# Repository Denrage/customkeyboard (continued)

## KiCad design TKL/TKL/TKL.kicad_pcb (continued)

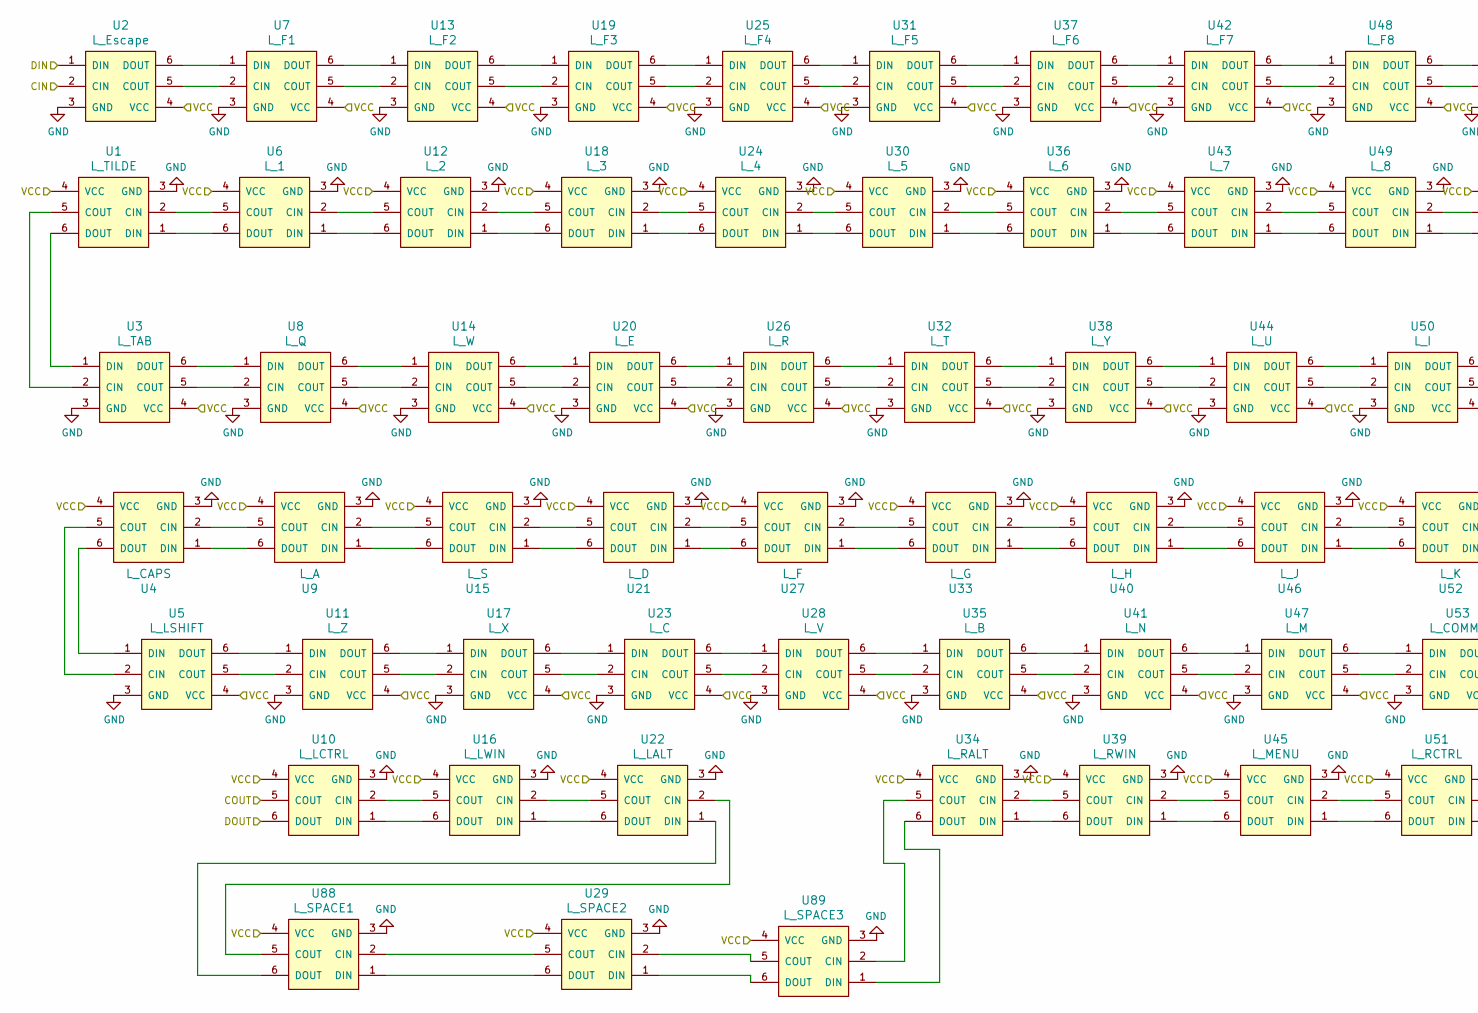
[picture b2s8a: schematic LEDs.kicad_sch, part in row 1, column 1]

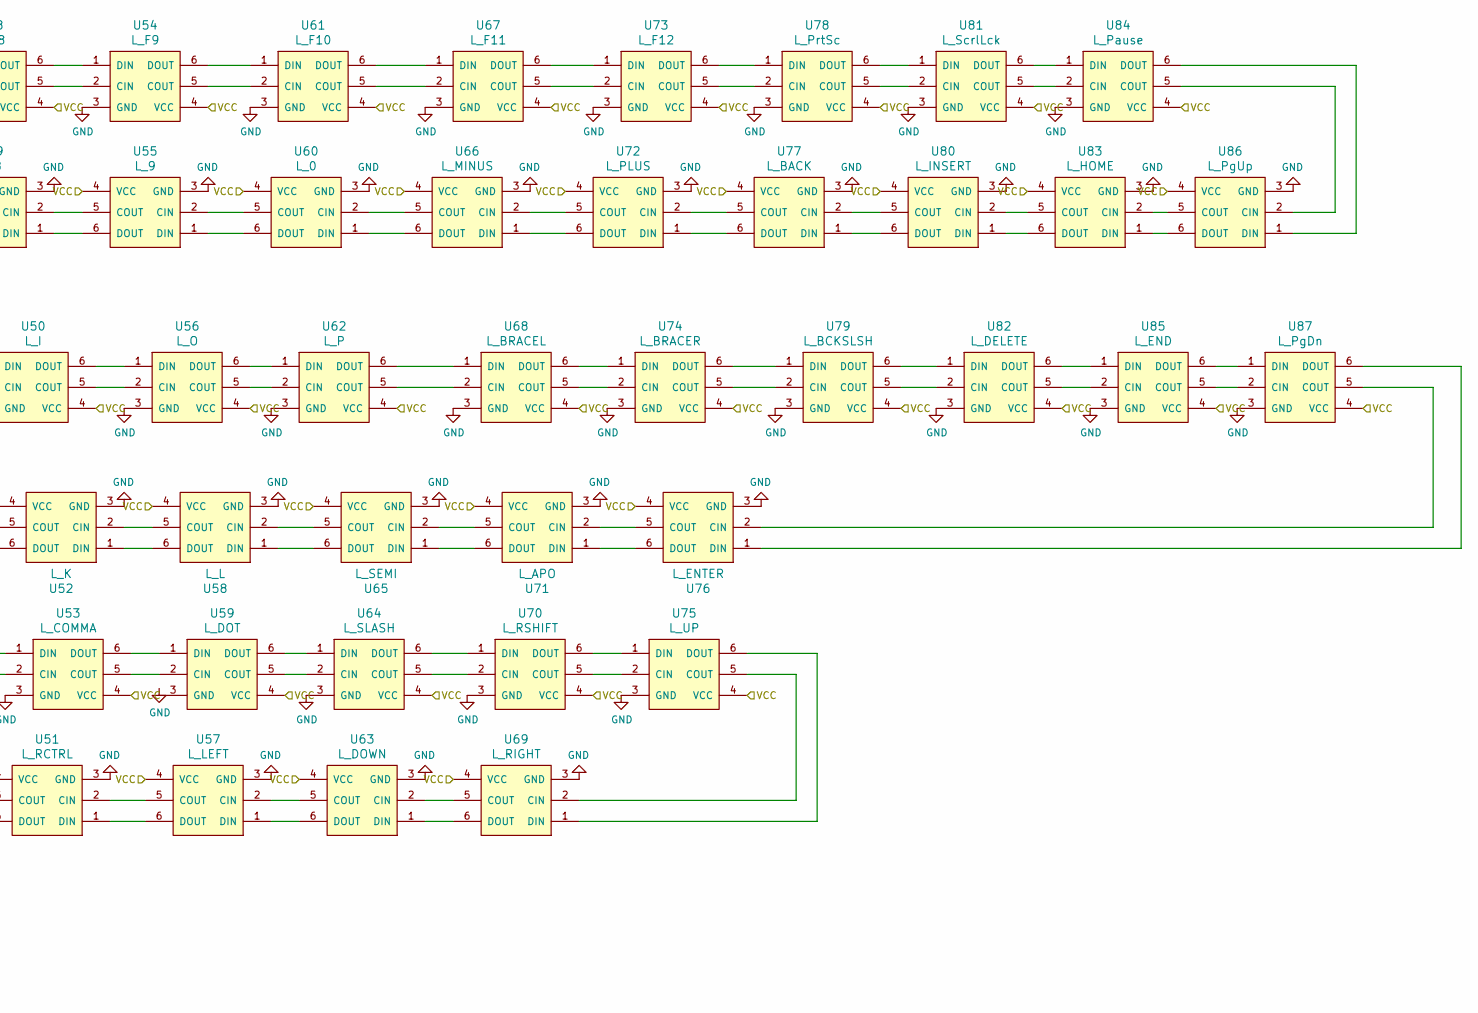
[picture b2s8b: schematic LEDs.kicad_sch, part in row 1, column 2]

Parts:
U1: L_TILDE; APA102
U2: L_Escape; APA102
U3: L_TAB; APA102
U4: L_CAPS; APA102
U5: L_LSHIFT; APA102
U6: L_1; APA102
U7: L_F1; APA102
U8: L_Q; APA102
U9: L_A; APA102
U10: L_LCTRL; APA102
U11: L_Z; APA102
U12: L_2; APA102
U13: L_F2; APA102
U14: L_W; APA102
U15: L_S; APA102
U16: L_LWIN; APA102
U17: L_X; APA102
U18: L_3; APA102
U19: L_F3; APA102
U20: L_E; APA102
U21: L_D; APA102
U22: L_LALT; APA102
U23: L_C; APA102
U24: L_4; APA102
U25: L_F4; APA102
U26: L_R; APA102
U27: L_F; APA102
U28: L_V; APA102
U29: L_SPACE2; APA102
U30: L_5; APA102
U31: L_F5; APA102
U32: L_T; APA102
U33: L_G; APA102
U34: L_RALT; APA102
U35: L_B; APA102
U36: L_6; APA102
U37: L_F6; APA102
U38: L_Y; APA102
U39: L_RWIN; APA102
U40: L_H; APA102
U41: L_N; APA102
U42: L_F7; APA102
U43: L_7; APA102
U44: L_U; APA102
U45: L_MENU; APA102
U46: L_J; APA102
U47: L_M; APA102
U48: L_F8; APA102
U49: L_8; APA102
U50: L_I; APA102
U51: L_RCTRL; APA102
U52: L_K; APA102
U53: L_COMMA; APA102
U54: L_F9; APA102
U55: L_9; APA102
U56: L_O; APA102
U57: L_LEFT; APA102
U58: L_L; APA102
U59: L_DOT; APA102
U60: L_0; APA102
U61: L_F10; APA102
U62: L_P; APA102
U63: L_DOWN; APA102
U64: L_SLASH; APA102
U65: L_SEMI; APA102
U66: L_MINUS; APA102
U67: L_F11; APA102
U68: L_BRACEL; APA102
U69: L_RIGHT; APA102
U70: L_RSHIFT; APA102
U71: L_APO; APA102
U72: L_PLUS; APA102
U73: L_F12; APA102
U74: L_BRACER; APA102
U75: L_UP; APA102
U76: L_ENTER; APA102
U77: L_BACK; APA102
U78: L_PrtSc; APA102
U79: L_BCKSLSH; APA102
U80: L_INSERT; APA102
U81: L_ScrlLck; APA102
U82: L_DELETE; APA102
U83: L_HOME; APA102
U84: L_Pause; APA102
U85: L_END; APA102
U86: L_PgUp; APA102
U87: L_PgDn; APA102
U88: L_SPACE1; APA102
U89: L_SPACE3; APA102

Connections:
CIN: U2.2 (CIN)
DIN: U2.1 (DIN)
GND: U1.3 (GND), U2.3 (GND), U3.3 (GND), U4.3 (GND), U5.3 (GND), U6.3 (GND), U7.3 (GND), U8.3 (GND), U9.3 (GND), U10.3 (GND), U11.3 (GND), U12.3 (GND), U13.3 (GND), U14.3 (GND), U15.3 (GND), U16.3 (GND), U17.3 (GND), U18.3 (GND), U19.3 (GND), U20.3 (GND), U21.3 (GND), U22.3 (GND), U23.3 (GND), U24.3 (GND), U25.3 (GND), U26.3 (GND), U27.3 (GND), U28.3 (GND), U29.3 (GND), U30.3 (GND), U31.3 (GND), U32.3 (GND), U33.3 (GND), U34.3 (GND), U35.3 (GND), U36.3 (GND), U37.3 (GND), U38.3 (GND), U39.3 (GND), U40.3 (GND), U41.3 (GND), U42.3 (GND), U43.3 (GND), U44.3 (GND), U45.3 (GND), U46.3 (GND), U47.3 (GND), U48.3 (GND), U49.3 (GND), U50.3 (GND), U51.3 (GND), U52.3 (GND), U53.3 (GND), U54.3 (GND), U55.3 (GND), U56.3 (GND), U57.3 (GND), U58.3 (GND), U60.3 (GND), U61.3 (GND), U62.3 (GND), U63.3 (GND), U64.3 (GND), U65.3 (GND), U66.3 (GND), U67.3 (GND), U68.3 (GND), U69.3 (GND), U70.3 (GND), U71.3 (GND), U72.3 (GND), U73.3 (GND), U74.3 (GND), U75.3 (GND), U76.3 (GND), U77.3 (GND), U78.3 (GND), U79.3 (GND), U80.3 (GND), U81.3 (GND), U82.3 (GND), U83.3 (GND), U84.3 (GND), U85.3 (GND), U86.3 (GND), U87.3 (GND), U88.3 (GND), U89.3 (GND)
unnamed: U1.1 (DIN), U6.6 (DOUT)
unnamed: U1.2 (CIN), U6.5 (COUT)
unnamed: U1.5 (COUT), U3.2 (CIN)
unnamed: U1.6 (DOUT), U3.1 (DIN)
unnamed: U2.5 (COUT), U7.2 (CIN)
unnamed: U2.6 (DOUT), U7.1 (DIN)
unnamed: U3.5 (COUT), U8.2 (CIN)
unnamed: U3.6 (DOUT), U8.1 (DIN)
unnamed: U4.1 (DIN), U9.6 (DOUT)
unnamed: U4.2 (CIN), U9.5 (COUT)
unnamed: U4.5 (COUT), U5.2 (CIN)
unnamed: U4.6 (DOUT), U5.1 (DIN)
unnamed: U10.1 (DIN), U16.6 (DOUT)
unnamed: U10.2 (CIN), U16.5 (COUT)
unnamed: U5.6 (DOUT), U11.1 (DIN)
unnamed: U5.5 (COUT), U11.2 (CIN)
unnamed: U11.5 (COUT), U17.2 (CIN)
unnamed: U11.6 (DOUT), U17.1 (DIN)
unnamed: U12.1 (DIN), U18.6 (DOUT)
unnamed: U12.2 (CIN), U18.5 (COUT)
unnamed: U6.2 (CIN), U12.5 (COUT)
unnamed: U6.1 (DIN), U12.6 (DOUT)
unnamed: U7.6 (DOUT), U13.1 (DIN)
unnamed: U7.5 (COUT), U13.2 (CIN)
unnamed: U13.5 (COUT), U19.2 (CIN)
unnamed: U13.6 (DOUT), U19.1 (DIN)
unnamed: U8.6 (DOUT), U14.1 (DIN)
unnamed: U8.5 (COUT), U14.2 (CIN)
unnamed: U14.5 (COUT), U20.2 (CIN)
unnamed: U14.6 (DOUT), U20.1 (DIN)
unnamed: U15.1 (DIN), U21.6 (DOUT)
unnamed: U15.2 (CIN), U21.5 (COUT)
unnamed: U9.2 (CIN), U15.5 (COUT)
unnamed: U9.1 (DIN), U15.6 (DOUT)
unnamed: U16.1 (DIN), U22.6 (DOUT)
unnamed: U16.2 (CIN), U22.5 (COUT)
unnamed: U17.5 (COUT), U23.2 (CIN)
unnamed: U17.6 (DOUT), U23.1 (DIN)
unnamed: U18.1 (DIN), U24.6 (DOUT)
unnamed: U18.2 (CIN), U24.5 (COUT)
unnamed: U19.5 (COUT), U25.2 (CIN)
unnamed: U19.6 (DOUT), U25.1 (DIN)
unnamed: U20.5 (COUT), U26.2 (CIN)
unnamed: U20.6 (DOUT), U26.1 (DIN)
unnamed: U21.1 (DIN), U27.6 (DOUT)
unnamed: U21.2 (CIN), U27.5 (COUT)
unnamed: U22.1 (DIN), U88.6 (DOUT)
unnamed: U22.2 (CIN), U88.5 (COUT)
unnamed: U23.5 (COUT), U28.2 (CIN)
unnamed: U23.6 (DOUT), U28.1 (DIN)
unnamed: U24.1 (DIN), U30.6 (DOUT)
unnamed: U24.2 (CIN), U30.5 (COUT)
unnamed: U25.5 (COUT), U31.2 (CIN)
unnamed: U25.6 (DOUT), U31.1 (DIN)
unnamed: U26.5 (COUT), U32.2 (CIN)
unnamed: U26.6 (DOUT), U32.1 (DIN)
unnamed: U27.1 (DIN), U33.6 (DOUT)
unnamed: U27.2 (CIN), U33.5 (COUT)
unnamed: U28.5 (COUT), U35.2 (CIN)
unnamed: U28.6 (DOUT), U35.1 (DIN)
unnamed: U29.1 (DIN), U89.6 (DOUT)
unnamed: U29.2 (CIN), U89.5 (COUT)
unnamed: U29.5 (COUT), U88.2 (CIN)
unnamed: U29.6 (DOUT), U88.1 (DIN)
unnamed: U30.1 (DIN), U36.6 (DOUT)
unnamed: U30.2 (CIN), U36.5 (COUT)
unnamed: U31.5 (COUT), U37.2 (CIN)
unnamed: U31.6 (DOUT), U37.1 (DIN)
unnamed: U32.5 (COUT), U38.2 (CIN)
unnamed: U32.6 (DOUT), U38.1 (DIN)
unnamed: U33.1 (DIN), U40.6 (DOUT)
unnamed: U33.2 (CIN), U40.5 (COUT)
unnamed: U34.1 (DIN), U39.6 (DOUT)
unnamed: U34.2 (CIN), U39.5 (COUT)
unnamed: U34.5 (COUT), U89.2 (CIN)
unnamed: U34.6 (DOUT), U89.1 (DIN)
unnamed: U35.5 (COUT), U41.2 (CIN)
unnamed: U35.6 (DOUT), U41.1 (DIN)
unnamed: U36.1 (DIN), U43.6 (DOUT)
unnamed: U36.2 (CIN), U43.5 (COUT)
unnamed: U37.5 (COUT), U42.2 (CIN)
unnamed: U37.6 (DOUT), U42.1 (DIN)
unnamed: U38.5 (COUT), U44.2 (CIN)
unnamed: U38.6 (DOUT), U44.1 (DIN)
unnamed: U39.1 (DIN), U45.6 (DOUT)
unnamed: U39.2 (CIN), U45.5 (COUT)
unnamed: U40.1 (DIN), U46.6 (DOUT)
unnamed: U40.2 (CIN), U46.5 (COUT)
unnamed: U41.5 (COUT), U47.2 (CIN)
unnamed: U41.6 (DOUT), U47.1 (DIN)
unnamed: U42.5 (COUT), U48.2 (CIN)
unnamed: U42.6 (DOUT), U48.1 (DIN)
unnamed: U43.1 (DIN), U49.6 (DOUT)
unnamed: U43.2 (CIN), U49.5 (COUT)
unnamed: U44.5 (COUT), U50.2 (CIN)
unnamed: U44.6 (DOUT), U50.1 (DIN)
unnamed: U45.1 (DIN), U51.6 (DOUT)
unnamed: U45.2 (CIN), U51.5 (COUT)
unnamed: U46.1 (DIN), U52.6 (DOUT)
unnamed: U46.2 (CIN), U52.5 (COUT)
unnamed: U47.5 (COUT), U53.2 (CIN)
unnamed: U47.6 (DOUT), U53.1 (DIN)
unnamed: U48.5 (COUT), U54.2 (CIN)
unnamed: U48.6 (DOUT), U54.1 (DIN)
unnamed: U49.1 (DIN), U55.6 (DOUT)
unnamed: U49.2 (CIN), U55.5 (COUT)
unnamed: U50.5 (COUT), U56.2 (CIN)
unnamed: U50.6 (DOUT), U56.1 (DIN)
unnamed: U51.1 (DIN), U57.6 (DOUT)
unnamed: U51.2 (CIN), U57.5 (COUT)
unnamed: U52.1 (DIN), U58.6 (DOUT)
unnamed: U52.2 (CIN), U58.5 (COUT)
unnamed: U53.5 (COUT), U59.2 (CIN)
unnamed: U53.6 (DOUT), U59.1 (DIN)
unnamed: U54.5 (COUT), U61.2 (CIN)
unnamed: U54.6 (DOUT), U61.1 (DIN)
unnamed: U55.1 (DIN), U60.6 (DOUT)
unnamed: U55.2 (CIN), U60.5 (COUT)
unnamed: U56.5 (COUT), U62.2 (CIN)
unnamed: U56.6 (DOUT), U62.1 (DIN)
unnamed: U57.1 (DIN), U63.6 (DOUT)
unnamed: U57.2 (CIN), U63.5 (COUT)
unnamed: U58.1 (DIN), U65.6 (DOUT)
unnamed: U58.2 (CIN), U65.5 (COUT)
unnamed: U59.5 (COUT), U64.2 (CIN)
unnamed: U59.6 (DOUT), U64.1 (DIN)
unnamed: U60.1 (DIN), U66.6 (DOUT)
unnamed: U60.2 (CIN), U66.5 (COUT)
unnamed: U61.5 (COUT), U67.2 (CIN)
unnamed: U61.6 (DOUT), U67.1 (DIN)
unnamed: U62.5 (COUT), U68.2 (CIN)
unnamed: U62.6 (DOUT), U68.1 (DIN)
unnamed: U63.1 (DIN), U69.6 (DOUT)
unnamed: U63.2 (CIN), U69.5 (COUT)
unnamed: U64.5 (COUT), U70.2 (CIN)
unnamed: U64.6 (DOUT), U70.1 (DIN)
unnamed: U65.1 (DIN), U71.6 (DOUT)
unnamed: U65.2 (CIN), U71.5 (COUT)
unnamed: U66.1 (DIN), U72.6 (DOUT)
unnamed: U66.2 (CIN), U72.5 (COUT)
unnamed: U67.5 (COUT), U73.2 (CIN)
unnamed: U67.6 (DOUT), U73.1 (DIN)
unnamed: U68.5 (COUT), U74.2 (CIN)
unnamed: U68.6 (DOUT), U74.1 (DIN)
unnamed: U69.1 (DIN), U75.6 (DOUT)
unnamed: U69.2 (CIN), U75.5 (COUT)
unnamed: U70.5 (COUT), U75.2 (CIN)
unnamed: U70.6 (DOUT), U75.1 (DIN)
unnamed: U71.1 (DIN), U76.6 (DOUT)
unnamed: U71.2 (CIN), U76.5 (COUT)
unnamed: U72.1 (DIN), U77.6 (DOUT)
unnamed: U72.2 (CIN), U77.5 (COUT)
unnamed: U73.5 (COUT), U78.2 (CIN)
unnamed: U73.6 (DOUT), U78.1 (DIN)
unnamed: U74.5 (COUT), U79.2 (CIN)
unnamed: U74.6 (DOUT), U79.1 (DIN)
unnamed: U76.1 (DIN), U87.6 (DOUT)
unnamed: U76.2 (CIN), U87.5 (COUT)
unnamed: U77.1 (DIN), U80.6 (DOUT)
unnamed: U77.2 (CIN), U80.5 (COUT)
unnamed: U78.5 (COUT), U81.2 (CIN)
unnamed: U78.6 (DOUT), U81.1 (DIN)
unnamed: U79.5 (COUT), U82.2 (CIN)
unnamed: U79.6 (DOUT), U82.1 (DIN)
unnamed: U80.1 (DIN), U83.6 (DOUT)
unnamed: U80.2 (CIN), U83.5 (COUT)
unnamed: U81.5 (COUT), U84.2 (CIN)
unnamed: U81.6 (DOUT), U84.1 (DIN)
unnamed: U82.5 (COUT), U85.2 (CIN)
unnamed: U82.6 (DOUT), U85.1 (DIN)
unnamed: U83.1 (DIN), U86.6 (DOUT)
unnamed: U83.2 (CIN), U86.5 (COUT)
unnamed: U84.5 (COUT), U86.2 (CIN)
unnamed: U84.6 (DOUT), U86.1 (DIN)
unnamed: U85.5 (COUT), U87.2 (CIN)
unnamed: U85.6 (DOUT), U87.1 (DIN)
VCC: U1.4 (VCC), U2.4 (VCC), U3.4 (VCC), U4.4 (VCC), U5.4 (VCC), U6.4 (VCC), U7.4 (VCC), U8.4 (VCC), U9.4 (VCC), U10.4 (VCC), U11.4 (VCC), U12.4 (VCC), U13.4 (VCC), U14.4 (VCC), U15.4 (VCC), U16.4 (VCC), U17.4 (VCC), U18.4 (VCC), U19.4 (VCC), U20.4 (VCC), U21.4 (VCC), U22.4 (VCC), U23.4 (VCC), U24.4 (VCC), U25.4 (VCC), U26.4 (VCC), U27.4 (VCC), U28.4 (VCC), U29.4 (VCC), U30.4 (VCC), U31.4 (VCC), U32.4 (VCC), U33.4 (VCC), U34.4 (VCC), U35.4 (VCC), U36.4 (VCC), U37.4 (VCC), U38.4 (VCC), U39.4 (VCC), U40.4 (VCC), U41.4 (VCC), U42.4 (VCC), U43.4 (VCC), U44.4 (VCC), U45.4 (VCC), U46.4 (VCC), U47.4 (VCC), U48.4 (VCC), U49.4 (VCC), U50.4 (VCC), U51.4 (VCC), U52.4 (VCC), U53.4 (VCC), U54.4 (VCC), U55.4 (VCC), U56.4 (VCC), U57.4 (VCC), U58.4 (VCC), U59.4 (VCC), U60.4 (VCC), U61.4 (VCC), U62.4 (VCC), U63.4 (VCC), U64.4 (VCC), U65.4 (VCC), U66.4 (VCC), U67.4 (VCC), U68.4 (VCC), U69.4 (VCC), U70.4 (VCC), U71.4 (VCC), U72.4 (VCC), U73.4 (VCC), U74.4 (VCC), U75.4 (VCC), U76.4 (VCC), U77.4 (VCC), U78.4 (VCC), U79.4 (VCC), U80.4 (VCC), U81.4 (VCC), U82.4 (VCC), U83.4 (VCC), U84.4 (VCC), U85.4 (VCC), U86.4 (VCC), U87.4 (VCC), U88.4 (VCC), U89.4 (VCC)

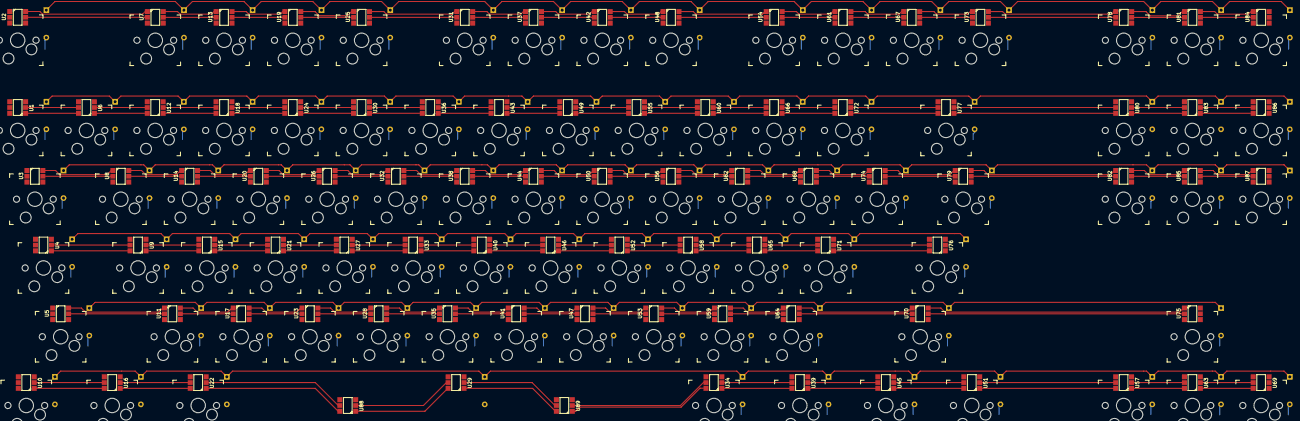
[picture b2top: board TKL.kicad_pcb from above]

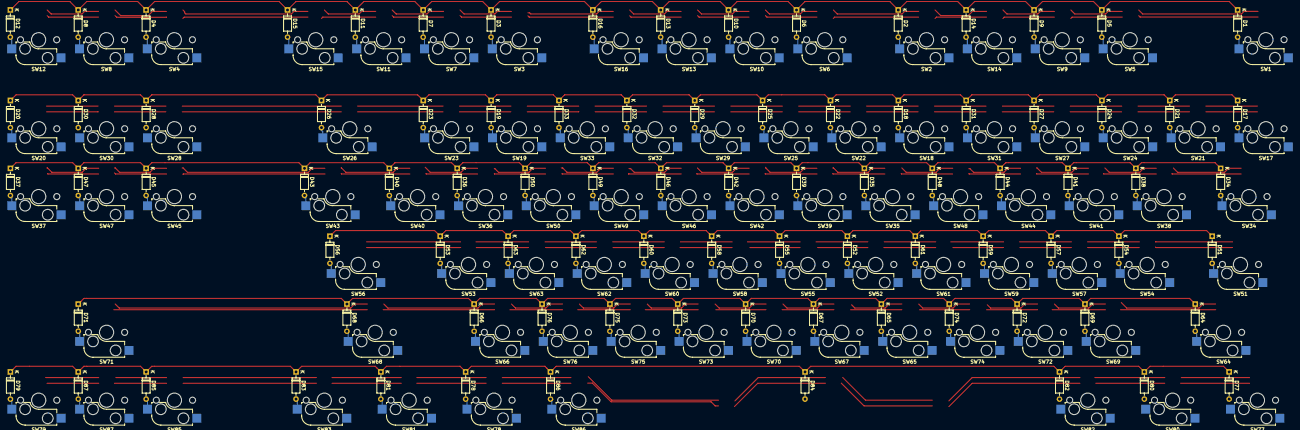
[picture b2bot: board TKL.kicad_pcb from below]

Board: 2 copper layers, 262 parts (87 on the bottom side), 288 nets.

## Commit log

2021-08-11 init
2021-08-11 extended readme
2021-08-11 Added kicad additional libraries
2021-08-11 Added needed components and tools to readme
2021-08-12 added usb and stm chip
2023-01-12 added qmk code
2023-01-19 Changed to APA102
2023-01-24 Finished numpad pcb
2023-01-24 Added Configurator for keyboard
2023-04-20 Added tkl keyboard
2023-04-22 Finishing touches tkl
2023-04-23 more finishing touches
2023-07-05 fixed numpad
2023-07-05 Added communication with keyboard
2023-07-05 cleanup
2023-07-05 Added tkl qmk firmware
2023-07-05 fixed tkl schematic
2023-07-05 prototype pcb
2023-07-05 Added type c connector
2023-07-05 added tkl case
2023-07-07 added usb model
2023-07-07 fixed led order
2023-07-07 added rgb
2023-07-07 added notes
2023-07-07 exported pcb
2023-07-07 Added case cad
2023-07-07 Added 3d models
2023-07-12 WIP: Added relationships to keycap plate
2023-10-12 Finished connecting keyboard plate lines
2023-10-12 Added via support
2024-01-06 temp
2024-04-28 Started fixing MCU
